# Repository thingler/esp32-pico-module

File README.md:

# Thingler ESP32-PICO Module

Thingler ESP32-PICO Module is a small size ESP32 development board with a minimum of required external components (including antenna). It's in the size of 20.60 mm x 15.60 mm with 16 pins and can be placed on a breadboard for prototyping. The module can be powered and programmed with the [Thingler ESP32 Programmer](https://github.com/thingler/esp32-programmer) but can also be powered with a separate power supply for small-sized designs.

Thingler ESP32 Programmer schematics and PCB has been designed with KiCad.

## Getting started

### Requirements

* [KiCad](https://kicad-pcb.org/download/) for the schematics

* [Thingler ESP32 Programmer](https://github.com/thingler/esp32-programmer)

### Pin configuration

Due to the size of the module, only part of the pins from the ESP32 microcontroller is exposed. Many of the ESP32 features can be configured to any of the I/O pins but some considerations has been made during the design of the module. Sice the ADC2 is shared with the WIFI module, which has higher priority, reading operation of adc2_get_raw() will fail between esp_wifi_start() and esp_wifi_stop(). Hence, three ADC1 channels have been exposed from the module in order to read ADC conversions during WIFI operation. Pins for I2S and DAC has also been exposed from the module.

Thingler ESP32-PICO Module has the following pin configuration:

| Name | Microcontroller pin(s) | Type | Function |
| --- | --- | --- | --- |
| 3V3 | 1, 3, 4, 19, 37, 43, 46 | P | Analog power supply (2.3V ~ 3.6V) |
| GND | 49 | P | Analog power supply (ground) |
| IO0 | 23 | I/O | ADC2_CH1, TOUCH1, RTC_GPIO11, CLK_OUT1, EMAC_TX_CLK |
| EN | 9 | I | High: On; enables the module, Low: Off; resets the module |
| RXD0 | 40 | I/O | GPIO3, U0RXD, CLK_OUT2 |
| TXD0 | 41 | I/O | GPIO1, U0TXD, CLK_OUT3, EMAC_RXD2 |
| IO33 | 13 | I/O | 32K_XN (32.768 kHz crystal oscillator output), ADC1_CH5, TOUCH8, RTC_GPIO8 |
| IO32 | 12 | I/O | 32K_XP (32.768 kHz crystal oscillator input), ADC1_CH4, TOUCH9, RTC_GPIO9 |
| IO25 | 14 | I/O | GPIO25, DAC_1, ADC2_CH8, RTC_GPIO6, EMAC_RXD0 |
| IO26 | 15 | I/O | GPIO26, DAC_2, ADC2_CH9, RTC_GPIO7, EMAC_RXD1 |
| IO37 | 6 | I | GPIO37, ADC1_CH1, RTC_GPIO1 |
| IO20 | 27 | I/O | GPIO20 |
| IO10 | 29 | I/O | GPIO10, SD_DATA3, HS1_DATA3, U1TXD |
| IO7 | 32 | I/O | GPIO7, SD_DATA0, HS1_DATA0, U2RTS |
| IO8 | 33 | I/O | GPIO8, SD_DATA1, HS1_DATA1, U2CTS |
| IO5 | 34 | I/O | GPIO5, VSPICS0, HS1_DATA6, EMAC_RX_CLK |

### Build

The PCB wihout components can be ordered from [Aisler](https://aisler.net/p/ZVKSJLOA) or the PCB can be ordered from any fabrication houses by providing the [gerber files](Gerbers).

The following components has been used for the module:

| Ref | Qty | Manufacturer Part Number | Manufacturer | Description | Product Link |
| --- | --- | --- | --- | --- | --- |
| U1 | 1 | ESP32-PICO-V3 | Espressif Systems | RF System on a Chip - SoC SIP module ESP32 with 4MByte Flash, Dual Core MCU, Wi-Fi & Bluetooth Combo, LGA48-pin, 7*7mm | [Mouser](https://www.mouser.fi/ProductDetail/Espressif-Systems/ESP32-PICO-V3?qs=%2Fha2pyFaduhAKW%252B0kbm4WirNln9M05hE2Cfek3joZqfvJDvo%252BkOm%252BA%3D%3D) |
| J1, J2 | 2 | 10129378-908002BLF | Amphenol FCI | Headers & Wire Housings ECONOSTIK HEADER SR VT TH 1X8 | [Mouser](https://www.mouser.fi/ProductDetail/Amphenol-FCI/10129378-908002BLF?qs=sGAEpiMZZMs%252BGHln7q6pm8Vn94ktop%2FJRLMW1D975zRqXbv0UaHrSw%3D%3D) |
| AE1 | 1 | 2450AT14A0100T | Johanson Technology | Antennas SMALL AREA 2.4G ANT | [Mouser](https://www.mouser.fi/ProductDetail/Johanson-Technology/2450AT14A0100T?qs=sGAEpiMZZMuBTKBKvsBmlN73K%2F2BcYXlKAGDK9p9NA4JvyuVwsRwMQ%3D%3D) |
| C1 | 1 | CGA4J1X7R0J106K125AC | TDK | 10 uF 10% 0805 6.3V | [Mouser](https://www.mouser.fi/ProductDetail/TDK/CGA4J1X7R0J106K125AC?qs=sGAEpiMZZMs0AnBnWHyRQEWjzA2rN6H9xJ%252BQ6n29nI0%3D) |
| C2, C4 | 2 | 885012207098 | Wurth Elektronik | 100 nF 10% 0805 50V | [Mouser](https://www.mouser.fi/ProductDetail/Wurth-Elektronik/885012207098?qs=sGAEpiMZZMs0AnBnWHyRQEGbLOF2VP1iyH0H1Hok68ReUt26c8JOqw%3D%3D) |
| R1 | 1 | CRCW080510K0FKEAC | Vishay / Dale | Thick Film Resistors - SMD 1/8Watt 10Kohms 1% Commercial Use | [Mouser](https://www.mouser.fi/ProductDetail/Vishay-Dale/CRCW080510K0FKEAC?qs=sGAEpiMZZMtlubZbdhIBIIZe04wfiaJWcT48uZO055s%3D) |

## License

Released under [GNU/GPL Version 3](LICENSE)

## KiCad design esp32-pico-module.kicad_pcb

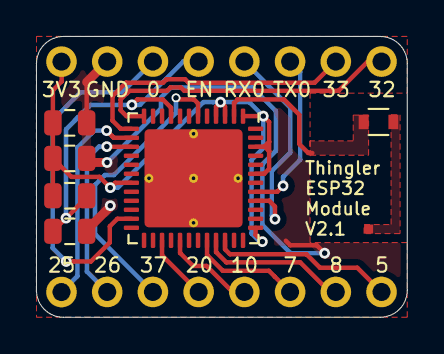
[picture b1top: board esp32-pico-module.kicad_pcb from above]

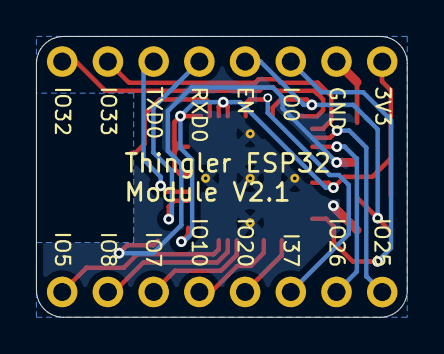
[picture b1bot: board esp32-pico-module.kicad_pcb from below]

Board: 2 copper layers, 20.6 x 15.6 mm, 9 parts (2 on the bottom side), 18 nets.

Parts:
AE1: Antenna_Chip; wifi antenna
C1: 10u; C_0805_2012Metric
C2, C4: 100n; C_0805_2012Metric
J1, J2: Conn_01x08_Male; PinHeader_1x08
R1: 10k; R_0805_2012Metric
U1: ESP32_PICO_V3; QFN-48
U2: Trace; AntennaTrace

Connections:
+3V3: C1.1, C2.1, J1.1, R1.1, U1.1, U1.3, U1.4, U1.19, U1.37, U1.43, U1.46
/EN: C4.1, J1.4, R1.2, U1.9
/I37: J2.3, U1.6
/IO0: J1.3, U1.23
/IO5: J2.8, U1.34
/IO7: J2.6, U1.32
/IO8: J2.7, U1.33
/IO10: J2.5, U1.29
/IO20: J2.4, U1.27
/IO25: J2.1, U1.14
/IO26: J2.2, U1.15
/IO32: J1.8, U1.12
/IO33: J1.7, U1.13
/RXD0: J1.5, U1.40
/TXD0: J1.6, U1.41
Earth: C1.2, C2.2, C4.2, J1.2, U1.49
unnamed: AE1.1, U1.2
unnamed: AE1.2, U2.1

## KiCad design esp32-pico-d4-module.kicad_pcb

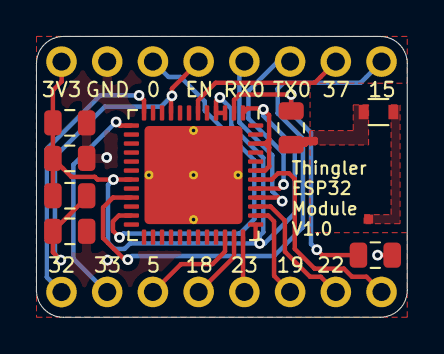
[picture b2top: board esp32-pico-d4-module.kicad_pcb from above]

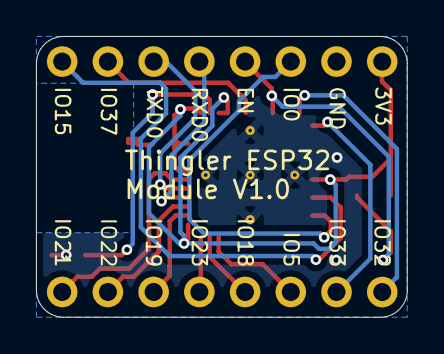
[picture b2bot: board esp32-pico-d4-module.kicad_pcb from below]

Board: 2 copper layers, 20.6 x 15.6 mm, 11 parts (2 on the bottom side), 19 nets.

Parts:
AE1: Antenna_Chip; wifi antenna
C1: 10u; C_0805_2012Metric
C2, C4: 100n; C_0805_2012Metric
C3: 8.2p; C_0805_2012Metric
J1, J2: Conn_01x08_Male; PinHeader_1x08
L1: 1.5n; L_0805_2012Metric
R1: 10k; R_0805_2012Metric
U1: ESP32_PICO-D4; QFN-48
U2: Trace; AntennaTrace

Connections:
+3V3: C1.1, C2.1, J1.1, R1.1, U1.1, U1.3, U1.4, U1.19, U1.37, U1.43, U1.46
/CAPP: J1.7, U1.6
/EN: C4.1, J1.4, R1.2, U1.9
/IO0: J1.3, U1.23
/IO5: J2.3, U1.34
/IO15: J1.8, U1.21
/IO18: J2.4, U1.35
/IO19: J2.6, U1.38
/IO21: J2.8, U1.42
/IO22: J2.7, U1.39
/IO23: J2.5, U1.36
/IO32: J2.1, U1.12
/IO33: J2.2, U1.13
/RXD0: J1.5, U1.40
/TXD0: J1.6, U1.41
Earth: C1.2, C2.2, C4.2, J1.2, L1.2, U1.49
unnamed: AE1.1, C3.2
unnamed: AE1.2, U2.1
unnamed: C3.1, L1.1, U1.2

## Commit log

2020-03-30 initial commit :tada:
2020-04-02 Documentations, license and improved silk screen
2020-04-02 power supply typo
2020-07-29 updated micrcontroller to use esp32-pico-v3
2020-12-23 Removed extra impedance components for the antenna
